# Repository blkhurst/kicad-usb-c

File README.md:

# USB-C Powered PCB

</a>
</a>

This **USB-C Powered AND Gate** is the first PCB I have designed using **KiCad**, and serves as a **proof of concept** for integrating USB-C power into future projects. The design includes:

- **USB-C Powered (5V)**
- **Power Indicator LED**
- **2 Tactile Buttons**
- **SN57HC08N IC (AND Gate)**
- **Output Indicator LED**

## Schematic & Layout

</a>
</a>

## **USB-C 16-Pin Connector**

Using the **GCT USB4215-03-A** USB-C receptacle, **created a custom KiCad symbol & footprint** using the **recommended PCB layout dimensions** from the [datasheet](https://www.mouser.co.uk/datasheet/2/837/usb4215-3472997.pdf).

</a>
</a>

| **Pin**         | **Description**                       |
| --------------- | ------------------------------------- |
| **VBUS (x4)**   | Power Supply                          |
| **CC1 / CC2**   | Configuration Channels                |
| **SBU1 / SBU2** | Sideband Accessory (HDMI, Audio, etc) |
| **DP1 / DP2**   | USB Data+                             |
| **DN1 / DN2**   | USB Data−                             |
| **GND (x4)**    | Ground                                |

- **CC1 & CC2** negotiate power delivery. Pulling them low via **5.1kΩ resistors** requests **5V** from the power source.
- **SBU1 & SBU2** left disconnected.
- **D+ & D- USB communication** left disconnected.

## **Future Projects**

- [ ] **USB-C Rechargeable Battery**: Featuring **power latch** and **charging indicator**.
- [ ] **USB-C ESP32-C3 Development Board**: ESP32 microcontrollers feature built-in **USB to JTAG / Serial**, allowing direct programming.
- [ ] **Development Board w/ Display**: Using an **FPC Connector** to connect a display.

## KiCad Tips

- Custom Symbol & Footprints
- Labels, Global Labels, Hierarchical Labels.
- GND Copper Fill
- Setting PCB Manufactures Design Rules / Capabilities.

## Resources

- [PCBWay Capabilities](https://www.pcbway.com/capabilities.html)
- [PCBWay Design Rules Download](https://www.pcbway.com/pcb_prototype/PCB_Design_Rule_Check.html)
- [Build a KiCad Project Schematic | Part 1 - HTM Workshop](https://www.youtube.com/watch?v=vLnu21fS22s)
- [Mastering KiCad: Design & Build Your Custom Stereo Amplifier Board](https://www.youtube.com/watch?v=RMPezTH0cck)

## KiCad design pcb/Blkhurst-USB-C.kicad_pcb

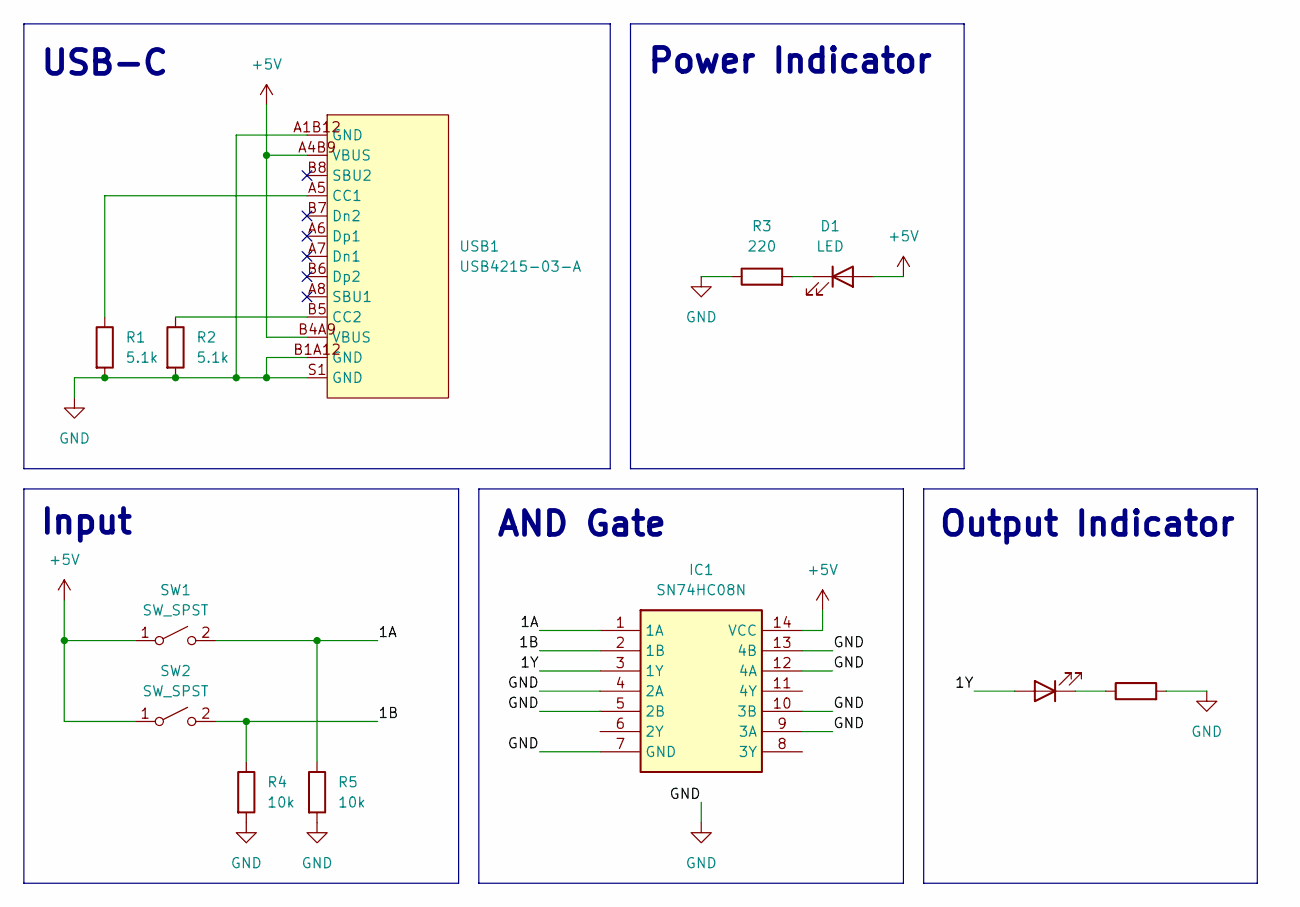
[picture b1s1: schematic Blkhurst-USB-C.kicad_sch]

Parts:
D1, D2: LED; LED_D5.0mm
IC1: SN74HC08N; DIP794W53P254L1930H508Q14N; Mouser Part Number 595-SN74HC08N
R1, R2: 5.1k; R_Axial_DIN0411_L9.9mm_D3.6mm_P12.70mm_Horizontal
R3, R6: 220; R_Axial_DIN0207_L6.3mm_D2.5mm_P7.62mm_Horizontal
R4, R5: 10k; R_Axial_DIN0207_L6.3mm_D2.5mm_P7.62mm_Horizontal
SW1, SW2: SW_SPST; SW_PUSH_6mm
USB1: USB4215-03-A

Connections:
+5V: D1.2 (A), IC1.14 (VCC), SW1.1 (A), SW2.1 (A), USB1.A4B9 (VBUS), USB1.B4A9 (VBUS)
/1A: IC1.1 (1A), R5.1, SW1.2 (B)
/1B: IC1.2 (1B), R4.1, SW2.2 (B)
/1Y: D2.2 (A), IC1.3 (1Y)
GND: IC1.4 (2A), IC1.5 (2B), IC1.7 (GND), IC1.9 (3A), IC1.10 (3B), IC1.12 (4A), IC1.13 (4B), R1.2, R2.2, R3.1, R4.2, R5.2, R6.2, USB1.A1B12 (GND), USB1.B1A12 (GND), USB1.S1 (GND)
unnamed: D1.1 (K), R3.2
unnamed: D2.1 (K), R6.1
unnamed: R1.1, USB1.A5 (CC1)
unnamed: R2.1, USB1.B5 (CC2)

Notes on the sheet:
Power Indicator
AND Gate
Input
Output Indicator
USB-C

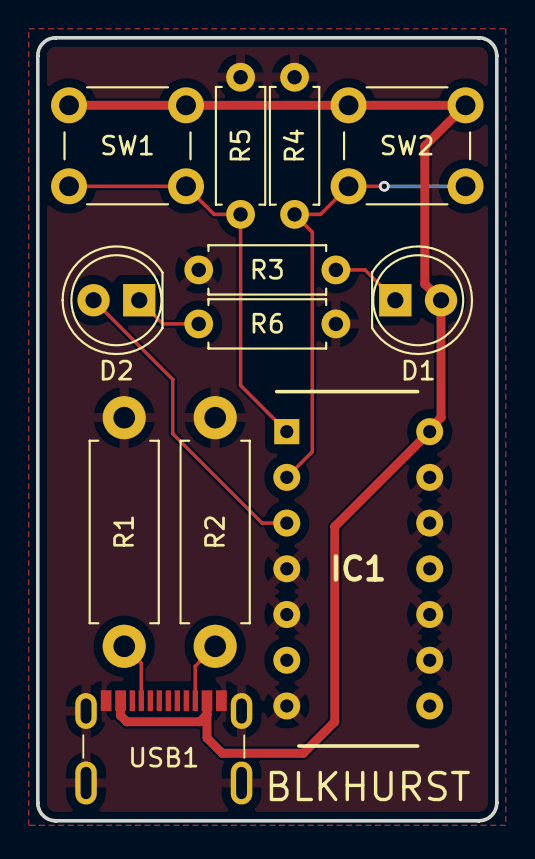
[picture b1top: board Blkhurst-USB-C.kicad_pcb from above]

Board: 2 copper layers, 25.5 x 43.5 mm, 12 parts (0 on the bottom side), 9 nets.
